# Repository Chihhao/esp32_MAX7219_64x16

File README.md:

# 💡 ESP32 MAX7219 LED Matrix Display

這是一個基於 ESP32 的 LED 點矩陣顯示專案，整合了 WiFi 網頁設定、RTC 時間顯示、以及條碼掃描器輸入功能，適合用於創客空間或資訊看板。  
本專案提供兩種顯示規格的程式碼：
1.  **64x16 (寬版)**: 使用 16 個 MAX7219 模組 (雙排)。
2.  **64x8 (窄版)**: 使用 8 個 MAX7219 模組 (單排)。

## 📸 專案展示 (Gallery)

### 寬版 (64x16)

### 窄版 (64x8)

---

## ✨ 功能特色 (Features)

*   **📶 WiFi AP 設定介面**:
    *   ESP32 啟動後建立獨立熱點 (AP)，方便手機或電腦連線設定。
    *   提供網頁介面修改三組輪播訊息及同步系統時間。
    *   設定內容儲存於 EEPROM，斷電後資料不遺失。
*   **ℹ️ 資訊顯示**:
    *   **輪播訊息**: 支援三組自訂文字訊息 (僅支援英文)，具備滾動與進場動畫效果。
    *   **時間顯示**: 內建 RTC 模組，可顯示大字體時間 (時:分) 與完整日期資訊。
    *   **雙區顯示**:
        *   **64x16**: 分為上下兩區 (Zone Upper / Zone Lower)。
        *   **64x8**: 分為左右兩區 (Zone Left / Zone Right)。
*   **🔫 條碼掃描互動**:
    *   支援 PS2 介面的條碼掃描器。
    *   掃描條碼後，螢幕會暫停輪播，立即顯示掃描到的內容 (停留 30 秒)。
*   **🌱 節能排程**:
    *   內建工作時間判斷，僅在 **08:30 ~ 17:30** 開啟顯示，其餘時間自動關閉以節省電力。

## 📦 版本說明 (Versions)

### 1. 64x16 寬版 (主要版本)
*   **程式碼路徑**: `esp32_MAX7219_64x16/`
*   **硬體配置**: 16 個 MAX7219 模組，排列為 64行 x 16列。
*   **顯示邏輯**: 上下兩行同步顯示或顯示不同資訊。

### 2. 64x8 窄版
*   **程式碼路徑**: `esp32_MAX7219_64x8/`
*   **硬體配置**: 8 個 MAX7219 模組，排列為 64行 x 8列 (單排)。
*   **顯示邏輯**:
    *   **左側 (Zone Left)**: 固定顯示時間 (時:分)。
    *   **右側 (Zone Right)**: 輪播文字訊息。

## 🛠️ 硬體與製作 (Hardware & Build)

### 📝 材料清單 (BOM)
1.  **微控制器**: NodeMCU-32S (ESP32)
2.  **顯示模組**: MAX7219 Dot Matrix Module (FC-16 形式)
    *   64x16 版本需 16 片 (或 4 組 4合1 模組串接)
    *   64x8 版本需 8 片
3.  **RTC 時鐘模組**: DS3231
4.  **輸入裝置**: PS2 介面條碼掃描器 (或 PS2 鍵盤) + PS/2 母座
    
5.  **電源供應**:
    *   **64x16 版本**: 建議使用 **5V 4A** (至少 3A)，以確保全亮時系統穩定。
    *   **64x8 版本**: 建議使用 **5V 2A**。
6.  **其他**:
    *   Reset Button
        
    *   PCB (可參考下方 Gerber 檔)
    *   3D 列印外殼
    *   強力磁鐵 (直徑 18.2mm / 厚 2mm)
    *   深色透明壓克力 (雷射切割)

### 🔌 接線說明 (Pinout)

| 模組 | 接腳名稱 | ESP32 GPIO | 備註 |
| :--- | :--- | :--- | :--- |
| **MAX7219** | CLK | 18 | SPI Clock |
| | DATA (DIN) | 23 | SPI MOSI |
| | CS | 5 | Chip Select |
| **PS2 Scanner** | Data | 36 | Input Only |
| | Clock | 39 | Input Only |
| **DS3231** | SDA | 21 | I2C SDA (Default) |
| | SCL | 22 | I2C SCL (Default) |

### 原理圖 (Schematic)

### PCB 設計

### 3D 外殼模型

* 寬版(64x16) Tinkercad Model: https://www.tinkercad.com/things/0vOz0woKdCv-
* 窄版(64x8) Tinkercad Model: https://www.tinkercad.com/things/j6S2HNCI5wD-

## 軟體設定 (Software Setup)

### 函式庫依賴
請在 Arduino IDE 中安裝以下函式庫：  
*註：版本號為開發時使用的版本，建議使用最新版，若有問題可嘗試回退。*  
1.  Arduino IDE :  1.8.19  
2.  ESP32 Board Library : 3.0.4  
3.  `MD_Parola` by MajicDesigns (v3.7.3)
4.  `MD_MAX72xx` by MajicDesigns (v3.5.1)
5.  `Bonezegei_DS3231` (v1.0.2)
6.  `PS2Keyboard` (v2.4)
7.  `Time` (TimeLib) (v1.6.1)

## 🚀 使用說明 (Usage)

1.  **⚡ 啟動**: 送電後，顯示器會顯示初始訊息或時間。
2.  **🔗 連線設定**:
    *   搜尋 WiFi SSID: `ESP32_LedDisplay` (64x16) 或 `LedDisplay_Nory` (64x8)
    *   密碼: `ESP32_LedDisplay` (64x16) 或 `LedDisplay_Nory` (64x8)
    *   *註：SSID 與密碼定義於程式碼開頭，可自行修改。*
3.  **🌐 網頁控制**:
    *   開啟瀏覽器，輸入網址 `http://192.168.4.1`
    *   **Text Setting**: 輸入 Message 1~3，點擊 "Send Text" 更新顯示。
    *   **Reset Time**: 點擊可將 ESP32 時間同步為目前瀏覽器裝置的時間。
4.  **🔢 條碼輸入**:
    *   直接使用連接的掃描器掃描條碼，螢幕將顯示 "Input: [條碼內容]"。

## ⚠️ 注意事項
*   **工作時間**: 若在 08:30 前或 17:30 後測試，螢幕將保持關閉。可修改程式碼中的 `isWorkTime()` 函式調整時段。
*   **PS2 接腳**: GPIO 36/39 為僅輸入 (Input Only) 接腳，適用於單向傳輸的掃描器。

---

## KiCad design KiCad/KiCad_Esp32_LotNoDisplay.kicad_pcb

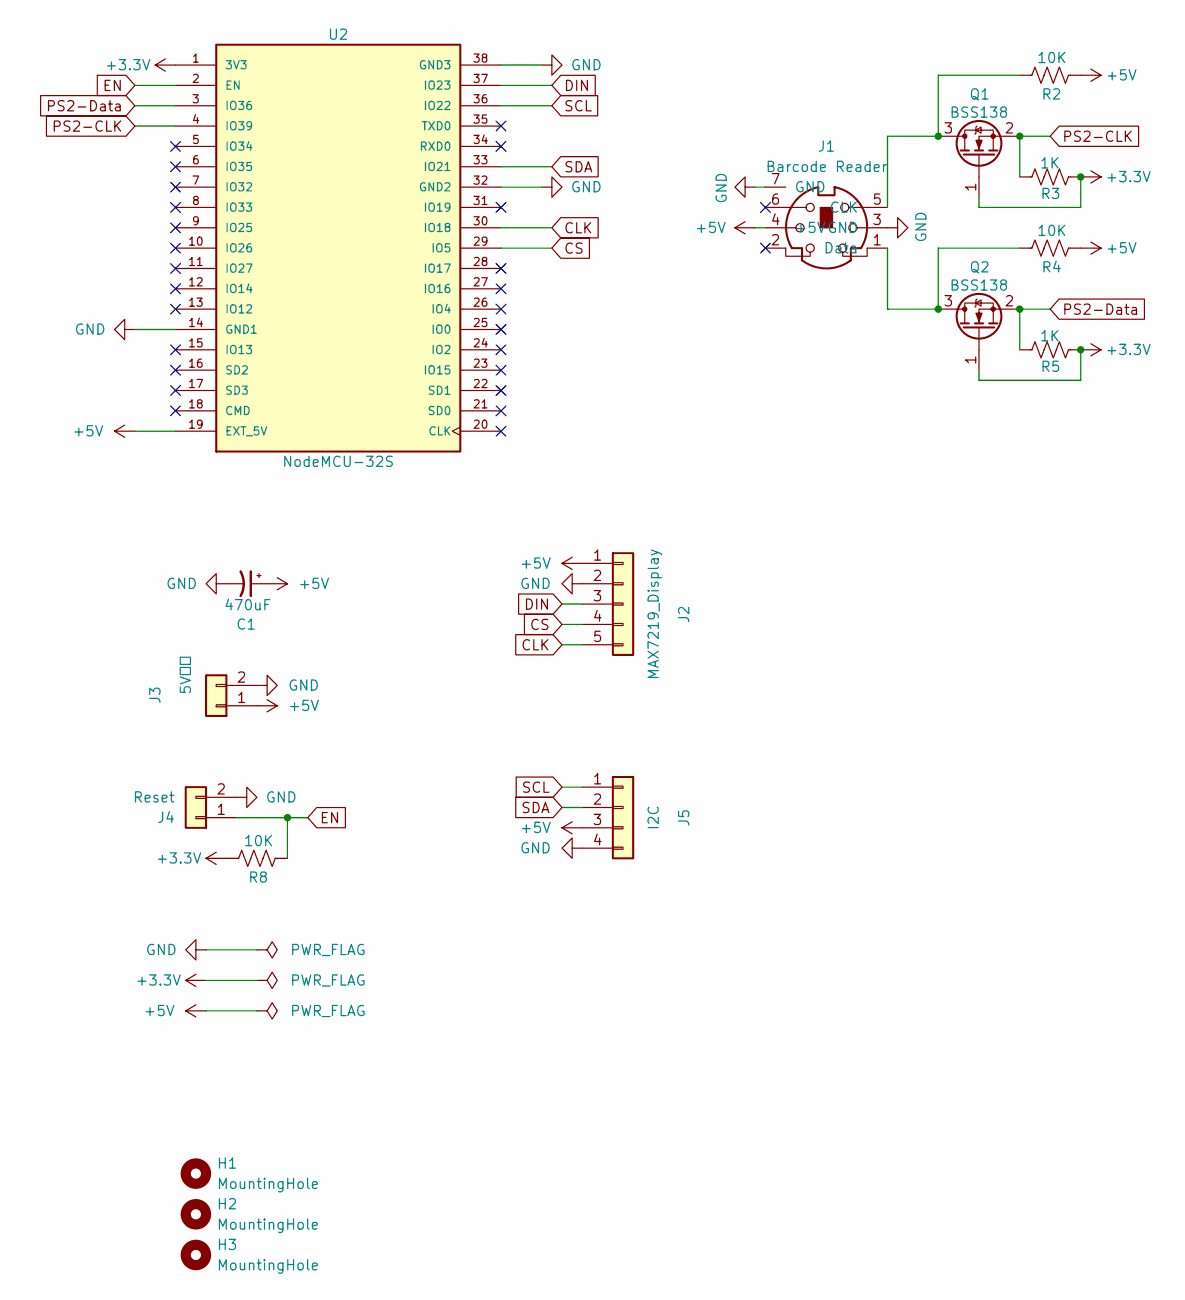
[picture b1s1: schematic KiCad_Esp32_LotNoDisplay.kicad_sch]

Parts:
C1: 470uF; CP_Radial_D10.0mm_P5.00mm
H1, H2, H3: MountingHole; MountingHole_3.2mm_M3_Pad_Via
J1: Barcode Reader; Connector_Mini-DIN_Female_6Pin_2rows
J2: MAX7219_Display; Molex_KK-254_AE-6410-04A_1x04_P2.54mm_Vertical
J3: 5V電源; TerminalBlock_Phoenix_MKDS-1,5-2-5.08_1x02_P5.08mm_Horizont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
J4: Reset; Molex_KK-254_AE-6410-02A_1x02_P2.54mm_Vertical
J5: I2C; Molex_KK-254_AE-6410-04A_1x04_P2.54mm_Vertical
Q1, Q2: BSS138; SOT-23
R2, R4, R8: 10K; R_0805_2012Metric_Pad1.20x1.40mm_HandSolder
R3, R5: 1K; R_0805_2012Metric_Pad1.20x1.40mm_HandSolder
U2: NodeMCU-32S; MODULE_ESP32-DEVKITC; PARTREV N/A

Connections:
+3.3V: Q1.1 (G), Q2.1 (G), R3.1, R5.1, R8.2, U2.1 (3V3)
+5V: C1.1, J1.4 (+5V), J2.1, J3.1, J5.3, R2.1, R4.1, U2.19 (EXT_5V)
CLK: J2.5, U2.30 (IO18)
CS: J2.4, U2.29 (IO5)
DIN: J2.3, U2.37 (IO23)
EN: J4.1, R8.1, U2.2 (EN)
GND: C1.2, J1.3 (GND), J1.7 (GND), J2.2, J3.2, J4.2, J5.4, U2.14 (GND1), U2.32 (GND2), U2.38 (GND3)
unnamed: J1.1 (Data), Q2.3 (D), R4.2
unnamed: J1.5 (CLK), Q1.3 (D), R2.2
PS2-CLK: Q1.2 (S), R3.2, U2.4 (IO39)
PS2-Data: Q2.2 (S), R5.2, U2.3 (IO36)
SCL: J5.1, U2.36 (IO22)
SDA: J5.2, U2.33 (IO21)

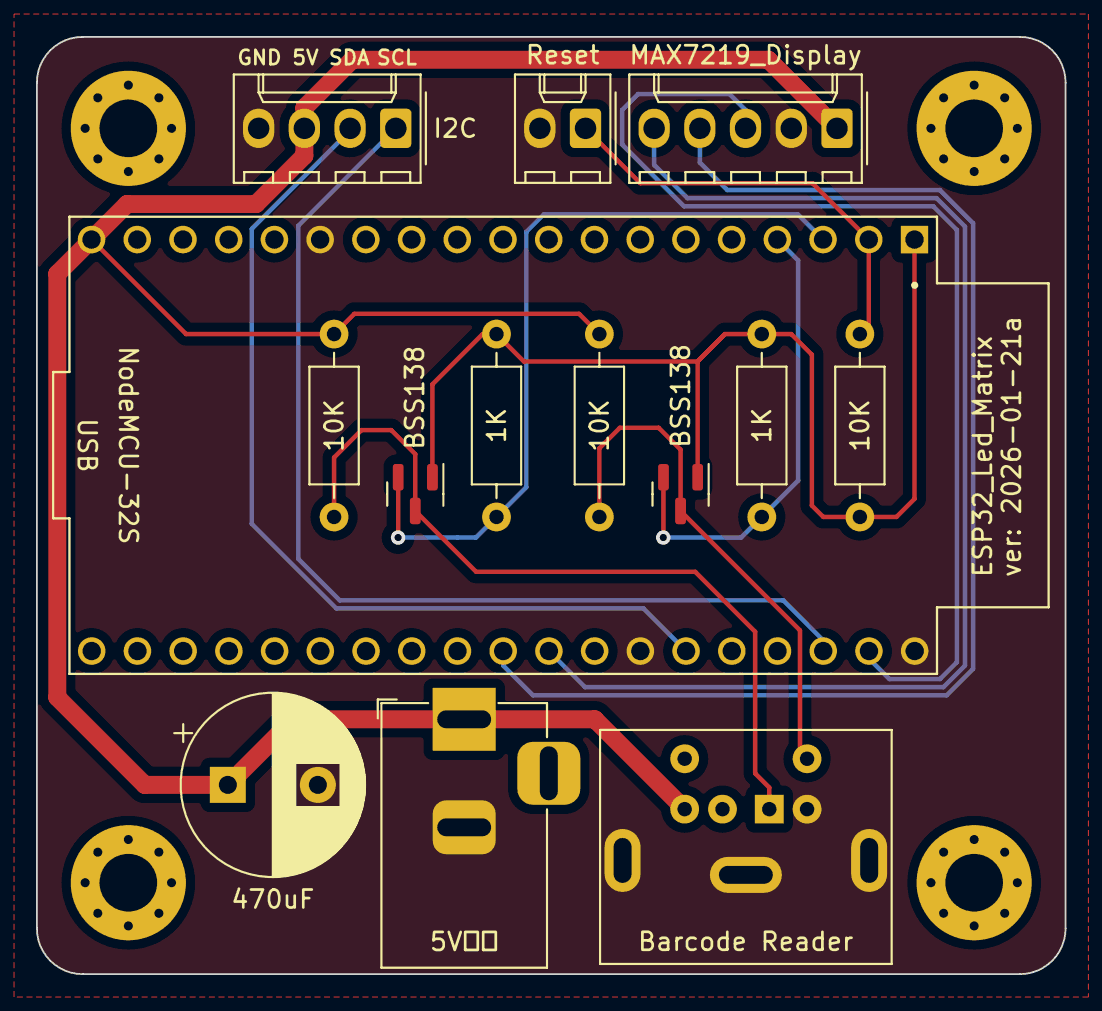
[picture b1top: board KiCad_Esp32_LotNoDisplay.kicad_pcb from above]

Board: 2 copper layers, 57.1 x 52.1 mm, 18 parts (0 on the bottom side), 13 nets.

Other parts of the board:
H4: MountingHole; MountingHole_3.2mm_M3_Pad_Via

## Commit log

2024-09-27 add pictures
2024-09-27 updated read me
2024-10-21 Update esp32_MAX7219_64x16.ino
    只有上班時間才點亮
2024-11-07 Update esp32_MAX7219_64x16.ino
    修正判斷上班時間的bug
2024-11-08 Add 64x8
2026-01-21 更新照片與私印
2026-01-21 Update images (optimized)
